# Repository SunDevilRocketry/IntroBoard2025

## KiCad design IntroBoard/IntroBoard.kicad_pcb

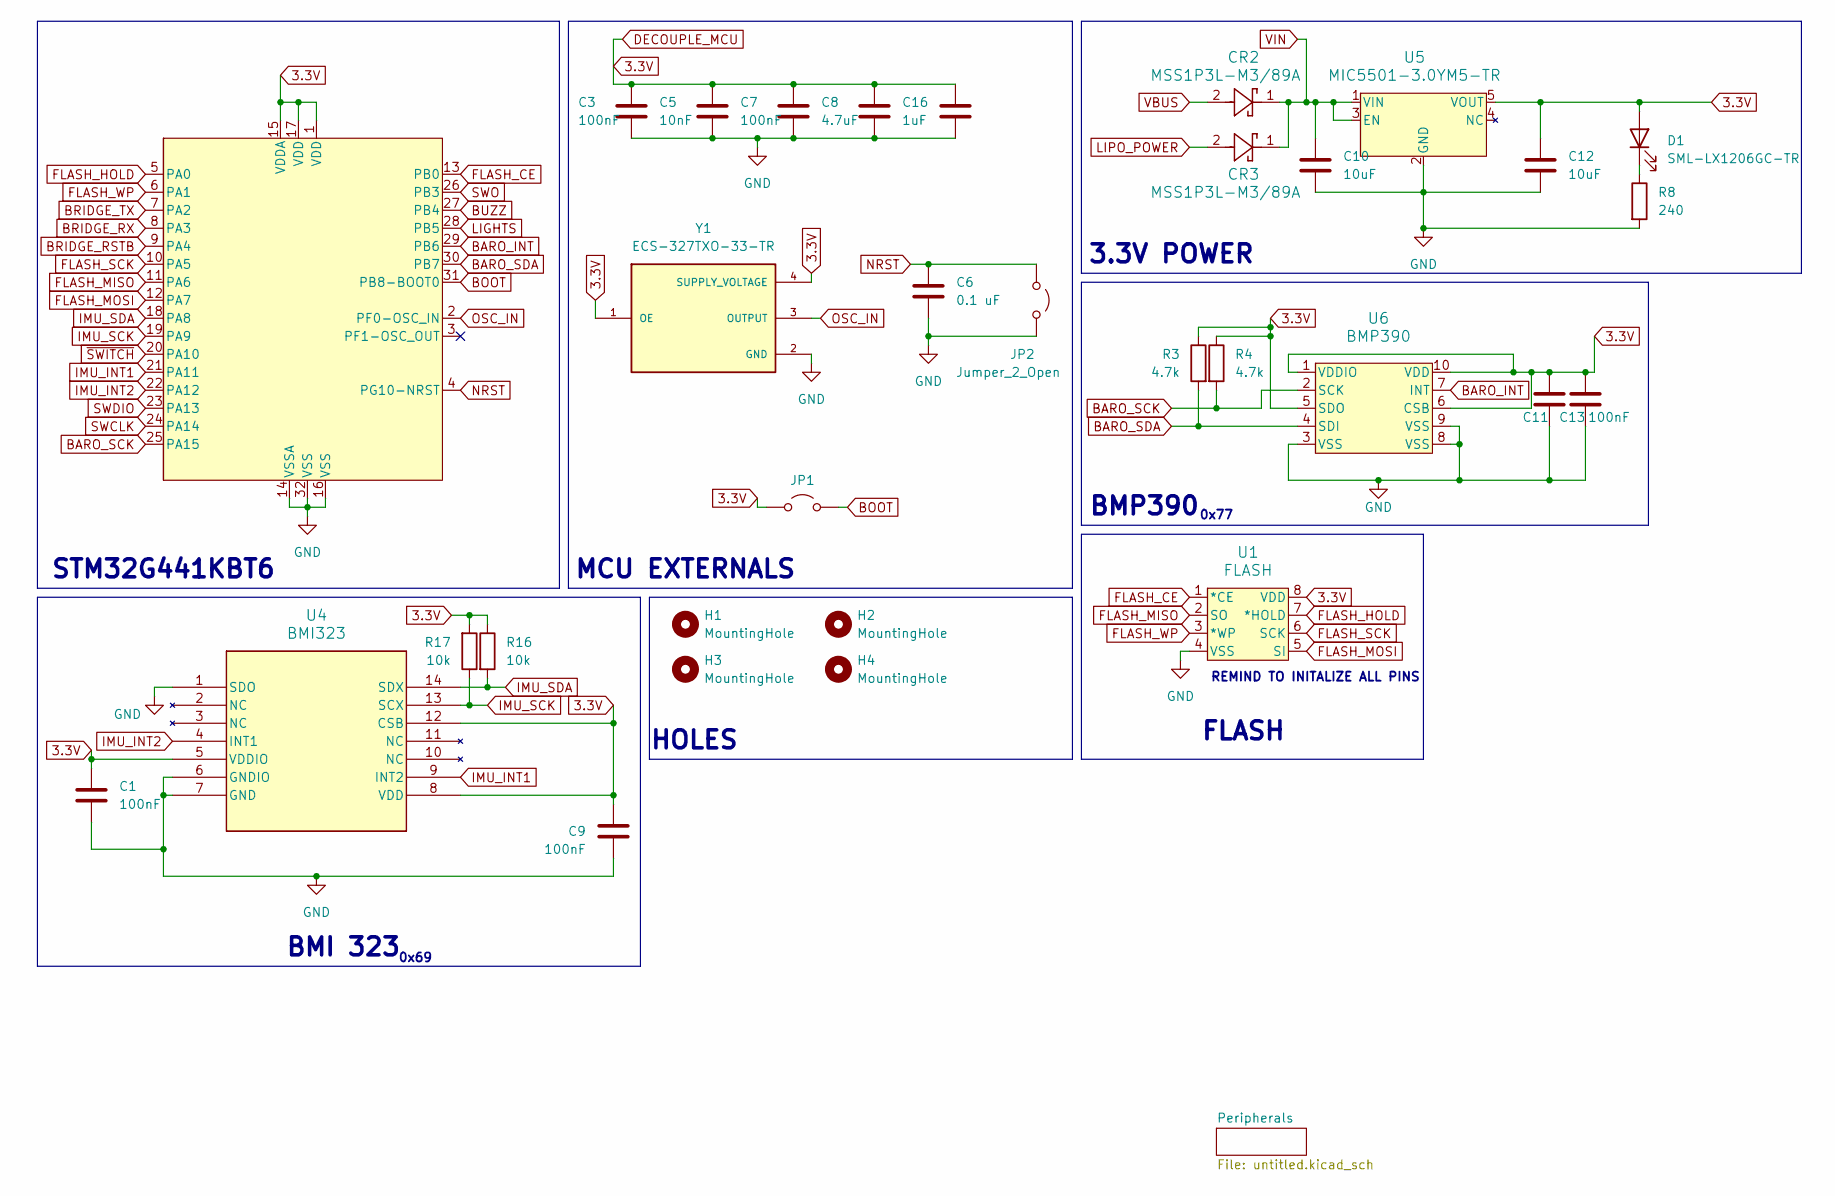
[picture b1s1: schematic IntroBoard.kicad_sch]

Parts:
C1, C3, C7, C9, C11, C13: 100nF; C_0603_1608Metric
C5: 10nF; C_0603_1608Metric
C6: 0.1 uF; C_0603_1608Metric
C8: 4.7uF; C_0603_1608Metric
C10, C12: 10uF; C_0603_1608Metric
C16: 1uF; C_0603_1608Metric
CR2, CR3: MSS1P3L-M3/89A; D_MicroSMP_AK
D1: SML-LX1206GC-TR; LED_0201_0603Metric
H1, H2, H3, H4: MountingHole; MountingHole_2.2mm_M2
JP1, JP2: Jumper_2_Open; TestPoint_2Pads_Pitch2.54mm_Drill0.8mm
R3, R4: 4.7k; R_0603_1608Metric
R8: 240; R_0603_1608Metric
R16, R17: 10k; R_0603_1608Metric
U1: FLASH; SOIC8_SA_SST_MCH
U2: STM32G441KBT6; LQFP-32
U4: BMI323; BMI323_BOS
U5: MIC5501-3.0YM5-TR; SOT23-5LD-PL-1_MCH
U6: BMP390; 10LGA_2X2X0p75_BOS
Y1: ECS-327TXO-33-TR; OSC_ECS-327TXO-33-TR; PARTREV Rev.2019

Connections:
3.3V: C1.1, C3.1, C5.1, C7.1, C8.1, C9.1, C11.1, C12.1, C13.1, C16.1, D1.2 (A), JP1.1 (A), R3.1, R4.1, R16.1, R17.2, U1.8 (VDD), U2.1 (VDD), U2.15 (VDDA), U2.17 (VDD), U4.5 (VDDIO), U4.8 (VDD), U4.12 (CSB), U5.5 (VOUT), U6.1 (VDDIO), U6.5 (SDO), U6.6 (CSB), U6.10 (VDD), Y1.1 (OE), Y1.4 (SUPPLY_VOLTAGE); also elsewhere on the board
BARO_INT: U2.29 (PB6), U6.7 (INT)
BARO_SCK: R4.2, U2.25 (PA15), U6.2 (SCK)
BARO_SDA: R3.2, U2.30 (PB7), U6.4 (SDI)
BOOT: JP1.2 (B), U2.31 (PB8-BOOT0)
BRIDGE_RSTB: U2.9 (PA4); also elsewhere on the board
BRIDGE_RX: U2.8 (PA3); also elsewhere on the board
BRIDGE_TX: U2.7 (PA2); also elsewhere on the board
BUZZ: U2.27 (PB4); also elsewhere on the board
FLASH_CE: U1.1 (*CE), U2.13 (PB0)
FLASH_HOLD: U1.7 (*HOLD), U2.5 (PA0)
FLASH_MISO: U1.2 (SO), U2.11 (PA6)
FLASH_MOSI: U1.5 (SI), U2.12 (PA7)
FLASH_SCK: U1.6 (SCK), U2.10 (PA5)
FLASH_WP: U1.3 (*WP), U2.6 (PA1)
GND: C1.2, C3.2, C5.2, C6.2, C7.2, C8.2, C9.2, C10.2, C11.2, C12.2, C13.2, C16.2, JP2.2 (B), R8.2, U1.4 (VSS), U2.14 (VSSA), U2.16 (VSS), U2.32 (VSS), U4.1 (SDO), U4.6 (GNDIO), U4.7 (GND), U5.2 (GND), U6.3 (VSS), U6.8 (VSS), U6.9 (VSS), Y1.2 (GND); also elsewhere on the board
IMU_INT1: U2.21 (PA11), U4.9 (INT2)
IMU_INT2: U2.22 (PA12), U4.4 (INT1)
IMU_SCK: R17.1, U2.19 (PA9), U4.13 (SCX)
IMU_SDA: R16.2, U2.18 (PA8), U4.14 (SDX)
LIGHTS: U2.28 (PB5); also elsewhere on the board
LIPO_POWER: CR3.2; also elsewhere on the board
NRST: C6.1, JP2.1 (A), U2.4 (PG10-NRST); also elsewhere on the board
unnamed: D1.1 (K), R8.1
OSC_IN: U2.2 (PF0-OSC_IN), Y1.3 (OUTPUT)
SWCLK: U2.24 (PA14); also elsewhere on the board
SWDIO: U2.23 (PA13); also elsewhere on the board
SWO: U2.26 (PB3); also elsewhere on the board
VBUS: CR2.2; also elsewhere on the board
VIN: C10.1, CR2.1, CR3.1, U5.1 (VIN), U5.3 (EN); also elsewhere on the board
~SWITCH: U2.20 (PA10); also elsewhere on the board

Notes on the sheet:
BMI 323
REMIND TO INITALIZE ALL PINS
HOLES
MCU EXTERNALS
STM32G441KBT6
FLASH
BMP390
0x77
3.3V POWER
0x69

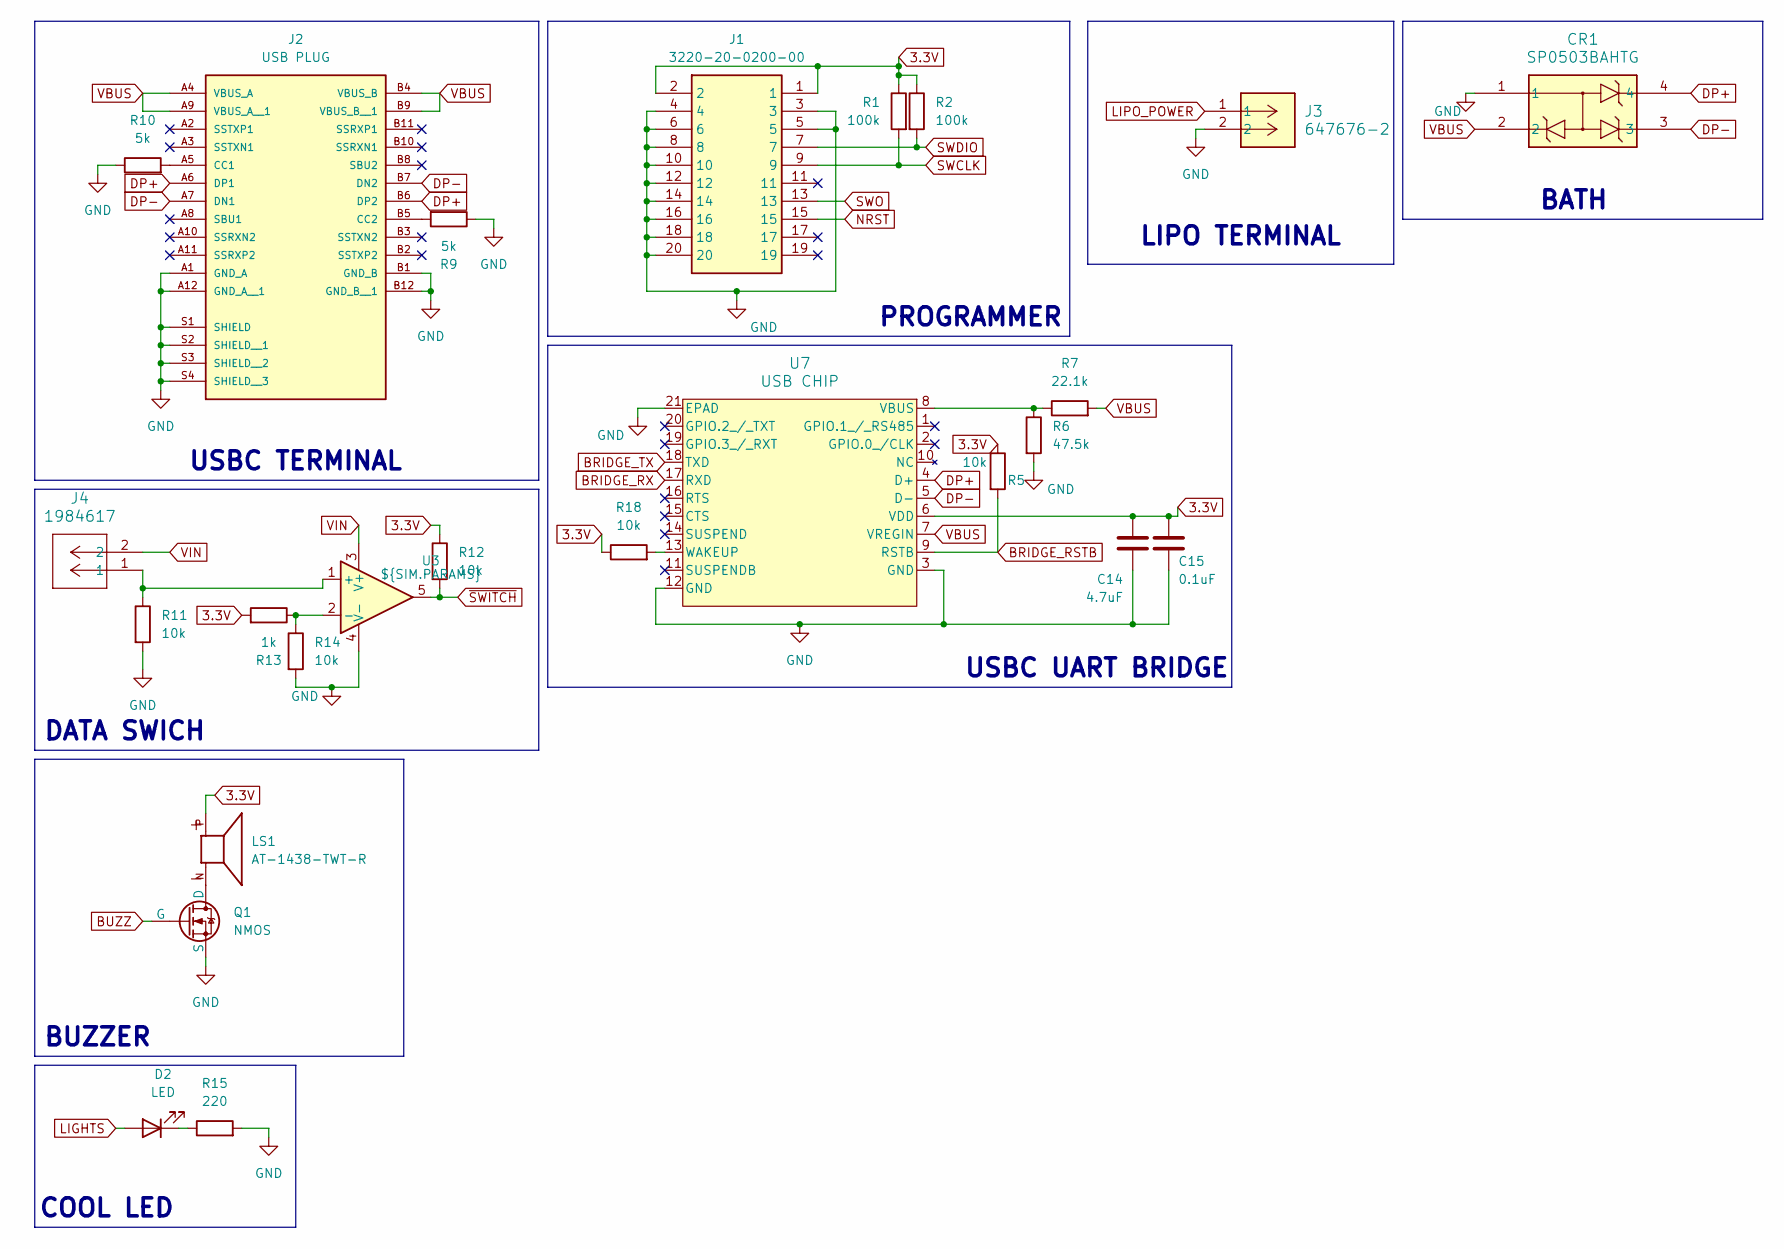
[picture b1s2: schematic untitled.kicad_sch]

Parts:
C14: 4.7uF; C_0603_1608Metric
C15: 0.1uF; C_0603_1608Metric
CR1: SP0503BAHTG; TVS-SP05_LTF
D2: LED; LED_0603_1608Metric
J1: 3220-20-0200-00; 322020020000; Manufacturer_Part_Number 3220-20-0200-00
J2: USB PLUG; AMPHENOL_10152803-00011LF; PARTREV A
J3: 647676-2; CONN2_647676-2_TEC
J4: 1984617; CONN_1984617_PXC
LS1: AT-1438-TWT-R; XDCR_AT-1438-TWT-R; PARTREV H
Q1: NMOS; SOT95P240X111-3N
R1, R2: 100k; R_0805_2012Metric
R5, R11, R12, R14, R18: 10k; R_0603_1608Metric
R6: 47.5k; R_0805_2012Metric
R7: 22.1k; R_0805_2012Metric
R9, R10: 5k; R_0603_1608Metric
R13: 1k; R_0603_1608Metric
R15: 220; R_0603_1608Metric
U3: ${SIM.PARAMS}; SOT23-5_STM
U7: USB CHIP; QFN20_CP2102N_SIL

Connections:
3.3V: C14.1, C15.1, J1.1, J1.2, LS1.P, R1.1, R2.1, R5.1, R12.1, R13.2, R18.1, U7.6 (VDD); also elsewhere on the board
BRIDGE_RSTB: R5.2, U7.9 (RSTB); also elsewhere on the board
BRIDGE_RX: U7.17 (RXD); also elsewhere on the board
BRIDGE_TX: U7.18 (TXD); also elsewhere on the board
BUZZ: Q1.2 (G); also elsewhere on the board
DP+: CR1.4, J2.A6 (DP1), J2.B6 (DP2), U7.4 (D+)
DP-: CR1.3, J2.A7 (DN1), J2.B7 (DN2), U7.5 (D-)
GND: C14.2, C15.2, CR1.1, J1.3, J1.4, J1.5, J1.6, J1.8, J1.10, J1.12, J1.14, J1.16, J1.18, J1.20, J2.A1 (GND_A), J2.A12 (GND_A__1), J2.B1 (GND_B), J2.B12 (GND_B__1), J2.S1 (SHIELD), J2.S2 (SHIELD__1), J2.S3 (SHIELD__2), J2.S4 (SHIELD__3), J3.2, Q1.3 (S), R6.2, R9.1, R10.1, R11.2, R14.2, R15.2, U3.4 (V-), U7.3 (GND), U7.12 (GND), U7.21 (EPAD); also elsewhere on the board
LIGHTS: D2.2 (A); also elsewhere on the board
LIPO_POWER: J3.1; also elsewhere on the board
NRST: J1.15; also elsewhere on the board
unnamed: D2.1 (K), R15.1
unnamed: J2.A5 (CC1), R10.2
unnamed: J2.B5 (CC2), R9.2
unnamed: LS1.N, Q1.1 (D)
unnamed: J4.1, R11.1, U3.1 (+)
unnamed: R13.1, R14.1, U3.2 (-)
unnamed: R6.1, R7.1, U7.8 (VBUS)
unnamed: R18.2, U7.13 (WAKEUP)
SWCLK: J1.9, R1.2; also elsewhere on the board
SWDIO: J1.7, R2.2; also elsewhere on the board
SWO: J1.13; also elsewhere on the board
VBUS: CR1.2, J2.A4 (VBUS_A), J2.A9 (VBUS_A__1), J2.B4 (VBUS_B), J2.B9 (VBUS_B__1), R7.2, U7.7 (VREGIN); also elsewhere on the board
VIN: J4.2, U3.3 (V+); also elsewhere on the board
~SWITCH: R12.2, U3.5; also elsewhere on the board

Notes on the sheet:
BATH
BUZZER
LIPO TERMINAL
DATA SWICH
COOL LED
USBC UART BRIDGE
USBC TERMINAL
PROGRAMMER

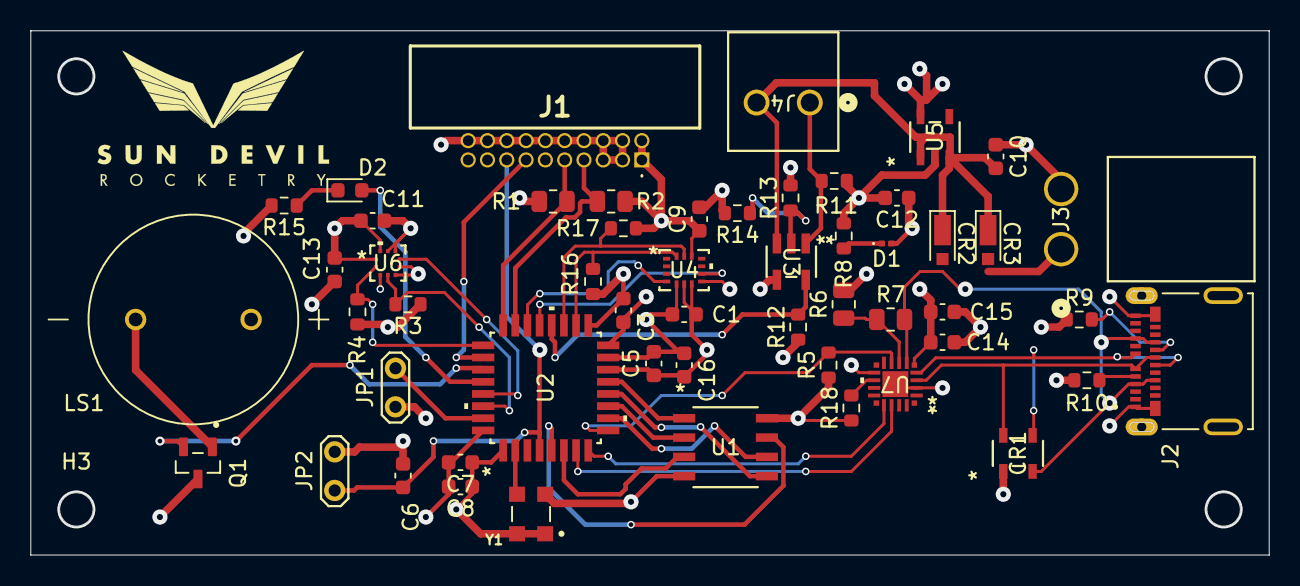
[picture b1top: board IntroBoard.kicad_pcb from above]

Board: 4 copper layers, 81.5 x 34.5 mm, 58 parts (0 on the bottom side), 41 nets.

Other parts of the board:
LOGO1: Logo

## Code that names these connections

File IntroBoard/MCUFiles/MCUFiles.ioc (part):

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Mcu.Name=STM32G441KBTx
Mcu.Package=LQFP32
Mcu.UserName=STM32G441KBTx
PA0.Signal=GPIO_Output
PA1.Signal=GPIO_Output
PA10.Signal=GPIO_Input
PA11.Signal=GPXTI11
PA12.Signal=GPXTI12
PA13.Mode=Trace_Asynchronous_SW
PA13.Signal=SYS_JTMS-SWDIO
PA14.Mode=Trace_Asynchronous_SW
PA14.Signal=SYS_JTCK-SWCLK
PA15.Mode=I2C
PA15.Signal=I2C1_SCL
PA2.Mode=Asynchronous
PA2.Signal=USART2_TX
PA3.Mode=Asynchronous
PA3.Signal=USART2_RX
PA4.Signal=GPIO_Output
PA5.Mode=Full_Duplex_Master
PA5.Signal=SPI1_SCK
PA6.Mode=Full_Duplex_Master
PA6.Signal=SPI1_MISO
PA7.Mode=Full_Duplex_Master
PA7.Signal=SPI1_MOSI
PA8.Mode=I2C
PA8.Signal=I2C2_SDA
PA9.Mode=I2C
PA9.Signal=I2C2_SCL
PB0.Signal=GPIO_Output
PB3.Mode=Trace_Asynchronous_SW
PB3.Signal=SYS_JTDO-SWO
PB4.Signal=GPIO_Output
PB5.Signal=GPIO_Output
PB6.Signal=GPXTI6
PB7.Mode=I2C
PB7.Signal=I2C1_SDA
PF0-OSC_IN.Mode=HSE-External-Clock-Source
PF0-OSC_IN.Signal=RCC_OSC_IN
RCC.HSE_VALUE=8000000
RCC.SYSCLKFreq_VALUE=16000000
board=custom

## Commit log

2025-07-28 Initial
    Initial commit V1
2025-08-08 1.1
    Quick fixes after review
2025-08-08 1.2
    Quickfix
2025-08-16 Final Touches
    Finished (theoretically) intro board
